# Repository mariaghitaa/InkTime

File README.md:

# Proiect InkTime Smartwatch

**Student:** Ghița Maria  
**Grupa:** 331CC

## 1. Descrierea Conceptului

InkTime este un dispozitiv purtabil bazat pe microcontrolerul **nRF52840**, conceput pentru a maximiza autonomia prin utilizarea unui ecran de tip **E-Paper (EPD)** de 1.54 inch. Spre deosebire de ecranele clasice, tehnologia E-Paper consumă energie doar la împrospătarea imaginii, oferind o vizibilitate excelentă în lumină naturală și un mod de operare "Always-on" extrem de eficient.

## 2. Diagrama Bloc (Hardware Architecture)

```text
                                  SISTEM INTELIGENT INKTIME
      SURSA ENERGIE              ___________________________                PERIFERICE (I/O)
    _________________           |                           |             ____________________
   |                 |          |      nRF52840 (SoC)       |            |                    |
   | USB-C Connector |--- 5V ---|   Bluetooth 5.0 Low En.   |--- SPI --->|  E-PAPER DISPLAY   |
   |   (Incarcare)   |          |___________________________|    Bus     |  (1.54" 24-pin)    |
   |_________________|           |  P0.02 (SCK)             |            |____________________|
            |                    |  P0.03 (MOSI)            |
            v                    |  P0.15 (DC)              |             ____________________
    _________________            |  P0.16 (RST)             |            |                    |
   | BQ25180 Charger |           |  P0.17 (BUSY)            |            |                    |
   | (Mngmnt Baterie)|-- VBAT -- |                          |            |                    |
   |_________________|    |      |  P0.26 (SDA) <---I2C---> |----------->|  ACCEL. (BMA421)   |
            ^             |      |  P0.27 (SCL)    Bus      |----------->|  GAUGE (MAX17048)  |
            |             |      |                          |----------->|  DRV2605 (Haptic)  |
    ________|________     |      |                          |            |____________________|
   | Li-Po Battery   |----+      |                          |
   |    250 mAh      |    |      |  P1.11 (PWM) ------------|----------->[ SHAKER / MOTOR ]
   |_________________|    |      |                          |
            |             |      |  P0.13 (UP)              |             ____________________
            v             |      |  P0.14 (ENTER) <---GPIO--|------------|   3x BUTOANE       |
    _________________     |      |  P1.02 (DOWN)            |            |   NAVIGATIE        |
   | RT6160A (Buck-B)|<---+      |                          |            |____________________|
   |  Output: 3.3V   |-----------|  P0.00 / P0.01 ----------|----------->[ CRYSTAL 32.768kHz]
   |_________________|           |  (LFXO Clock)            |            
                                 |__________________________|
```

## 3. Descriere Detaliată Hardware

### 3.1 Microcontroller — nRF52840

Inima sistemului este microcontrollerul Nordic nRF52840, care gestionează toate perifericele, comunicația wireless și logica aplicației.

- **CPU:** ARM Cortex-M4F la frecvență maximă de 64 MHz
- **Memorie:** 1 MB Flash, 256 KB RAM
- **Alimentare:** 3.3V (furnizat de regulatorul DC-DC)
- **Conectivitate:** Bluetooth 5.0 Low Energy, USB 2.0
- **Periferice utilizate:** SPI, I2C, GPIO, PWM, USB

Antena ceramică 2450AT18B100E (2.4 GHz) este acordată printr-o rețea de matching LC calculată pentru impedanță de 50Ω, asigurând performanță RF optimă.

### 3.2 Sistemul de Alimentare

#### Baterie LiPo

Dispozitivul este alimentat de o baterie LiPo cu tensiune nominală de 3.7V (max 4.2V) și capacitate de 250 mAh.

#### Încărcător — BQ25180

Încărcarea bateriei se realizează prin circuitul BQ25180 care primește alimentare de la conectorul USB-C. Acesta oferă management complet al ciclului de încărcare, protecție termică și reglare a curentului de încărcare pentru bateria LiPo. Comunicarea cu MCU-ul se face prin I2C, permițând configurarea parametrilor de încărcare din software.

#### Convertor DC-DC — RT6160A

Regulatorul buck-boost RT6160A convertește tensiunea variabilă a bateriei (3.0–4.2V) într-o ieșire stabilă de 3.3V. Alegerea unui convertor buck-boost (în loc de un LDO) asigură funcționarea stabilă a întregului sistem inclusiv când bateria este aproape descărcată. Tensiunea de 3.3V alimentează MCU-ul, senzorii, display-ul și toate celelalte periferice.

#### Fuel Gauge — MAX17048

Monitorizarea stării bateriei este realizată de MAX17048, care utilizează algoritmul ModelGauge pentru a estima nivelul de încărcare (State of Charge) fără a necesita rezistență de shunt. Comunicarea se face prin I2C, iar pinul ALERT (conectat la P0.10 pe MCU) poate genera o întrerupere atunci când nivelul bateriei scade sub un prag configurat.

### 3.3 Interfața USB-C

Conectorul USB Type-C (KH-TYPE-C-16P) îndeplinește două roluri: alimentare pentru încărcarea bateriei și comunicație USB 2.0 cu MCU-ul. Liniile de date D+ și D- sunt conectate la pinii USB dedicați ai nRF52840, iar pe liniile CC1/CC2 sunt montate rezistențe pull-down de 5.1kΩ pentru identificarea rolului de device. Protecția ESD pe liniile USB este asigurată de circuitul USBLC6-2SC6Y.

### 3.4 Display E-Paper

Display-ul e-paper de 1.54 inch este conectat prin FPC (conector Molex 503480-2400, 24-pin). Principalele avantaje ale tehnologiei e-paper pentru un smartwatch sunt consumul aproape zero în idle (imaginea persistă fără alimentare) și lizibilitatea excelentă în lumina solară.

Comunicarea cu MCU-ul se face prin **SPI** cu următoarele semnale:

- **MOSI** — transmite date și comenzi către display
- **SCK** — semnal de clock pentru sincronizarea transferului
- **DC** — diferențiază între comenzi și date
- **RST** — resetare hardware a controllerului display-ului
- **BUSY** — semnalizează că display-ul procesează un refresh

Alimentarea display-ului este controlată de un PFET Si2301CDS, permițând oprirea completă a panoului pentru economisirea energiei. Circuitul driver integrat pe placa EPD generează tensiunile înalte necesare actualizării cernelii electronice.

### 3.5 Accelerometru — BMA421

Senzorul BMA421 oferă măsurători de accelerație pe 3 axe și este utilizat pentru:

- detecția mișcării și a gesturilor (ridicare încheietură)
- funcționalitate de pedometru
- activarea ecranului din sleep

Comunicarea se face prin **I2C** (SDA, SCL), iar senzorul dispune de două linii de întrerupere (INT1, INT2) care permit trezirea MCU-ului din modul de consum redus doar când apare un eveniment relevant.

### 3.6 Driver Haptic — DRV2605

Driverul DRV2605 controlează motorul de vibrație (LRA/ERM) și oferă o bibliotecă de peste 100 de efecte haptice predefinite. Configurarea efectelor se realizează prin **I2C**, iar activarea vibrației se poate face și direct printr-un semnal digital pe pinul EN, fără a necesita comunicare I2C continuă.

### 3.7 Butoane

Trei butoane tactile (EVP-AKB31A) sunt conectate la pini GPIO ai MCU-ului cu rezistențe pull-up de 10kΩ. La apăsare, butonul conectează pinul la masă, iar MCU-ul detectează tranziția HIGH→LOW. Fiecare buton are un condensator de debouncing de 1µF.

- **UP** — navigare sus în meniu
- **ENTER** — selecție / confirmare
- **DOWN** — navigare jos în meniu

### 3.8 Interfața SWD

Programarea și debugging-ul firmware-ului se realizează prin interfața SWD (Serial Wire Debug) accesibilă printr-un header Tag-Connect TC2030-IDC (6-pin). Semnalele utilizate: SWDIO, SWDCLK, RESET, VCC, GND.

## 4. Bill of Materials (BOM)

| Componentă | Package | JLC Parts | Datasheet |
|------------|---------|-----------|-----------|
| Antenna (2450AT18B100E) | SMD 3216 | [C5179427](https://jlcpcb.com/partdetail/C5179427) | [Datasheet](https://www.johansontechnology.com/datasheets/2450AT18B100/2450AT18B100.pdf) |
| Charger (BQ25120YBGR) | DSBGA-9 | [C1682423](https://jlcpcb.com/partdetail/C1682423) | [Datasheet](https://www.ti.com/lit/ds/symlink/bq25180.pdf) |
| Haptic Driver (DRV2605LDGSR) | VSSOP-10 | [C527464](https://jlcpcb.com/partdetail/C527464) | [Datasheet](https://www.ti.com/lit/ds/symlink/drv2605l.pdf) |
| Buttons (EVP-AKB31A) | SMD tactile | [C2845028](https://jlcpcb.com/partdetail/C2845028) | [Datasheet](https://industrial.panasonic.com/cdbs/www-data/pdf/ATV0000/ATV0000CE3.pdf) |
| USB Type-C Connector (KH-TYPE-C-16P) | 16-pin SMD | [C2765186](https://jlcpcb.com/partdetail/C2765186) | [Datasheet](https://datasheet.lcsc.com/lcsc/2012121836_Kinghelm-KH-TYPE-C-16P_C2765186.pdf) |
| Fuel Gauge (MAX17048G+T10) | DFN-8 (2x2) | [C2682616](https://jlcpcb.com/partdetail/C2682616) | [Datasheet](https://www.analog.com/media/en/technical-documentation/data-sheets/MAX17048-MAX17049.pdf) |
| MCU (nRF52840-QIAA-R) | aQFN73 (7x7) | [C190794](https://jlcpcb.com/partdetail/C190794) | [Datasheet](https://docs.nordicsemi.com/) |
| Accelerometer (BMA421) | LGA-12 (2x2) | [C5242966](https://jlcpcb.com/partdetail/C5242966) | [Datasheet](https://www.bosch-sensortec.com/media/boschsensortec/downloads/datasheets/bst-bma421-ds004.pdf) |
| FPC Connector (Molex 503480-2400) | 24-pin 0.5mm FPC | [C2857168](https://jlcpcb.com/partdetail/C2857168) | [Datasheet](https://www.molex.com/en-us/products/part-detail/5034802400) |
| Buck-Boost Regulator (RT6160AWSC) | WLCSP-15 | [C7065276](https://jlcpcb.com/partdetail/C7065276) | [Datasheet](https://www.richtek.com/assets/product_file/RT6160A/DS6160A-05.pdf) |
| Vibration Motor (LCM102733605F) | Wire leads | [C7528006](https://jlcpcb.com/partdetail/C7528006) | [Datasheet](https://datasheet.lcsc.com/lcsc/2310131633_LCM-LCM1027B3605F_C7528806.pdf) |
| PFET EPD power (Si2301CDS) | SOT-23 | [C10487](https://jlcpcb.com/partdetail/C10487) | [Datasheet](https://www.vishay.com/docs/68749/si2301cds.pdf) |
| USB ESD Protection (USBLC6-2SC6Y) | SOT-23-6 | [C7519](https://jlcpcb.com/partdetail/C7519) | [Datasheet](https://www.st.com/resource/en/datasheet/usblc6-2.pdf) |
| SWD Debug Header (TC2030-IDC) | Tag-Connect 6-pin | - | - |
| Crystal 32 MHz | 2016 | - | - |
| Crystal 32.768 kHz | 3215 | - | - |
| Resistors x 2 10k | 0201 | - | - |
| Resistors x 2 5.1k | 0201 | - | - |
| Capacitors x 4 12pF | 0201 | - | - |
| Capacitors x 5 100nF | 0201 | - | - |
| Capacitors x 5 4.7uF | 0402 | - | - |
| Capacitors x 2 22uF | 0402 | - | - |
| Capacitors x 12 1uF | 0402 | - | - |
| Inductor 0.47uH | 2012 | - | - |
| Inductor 10uH | 0402 | - | - |
| E-Paper Display 1.54 inch | 24-pin FPC | - | - |
| LiPo Battery 250 mAh | - | - | - |

## 5. Alocare Pini nRF52840

### 5.1 Interfața SPI — Display E-Paper

| Pin | Semnal | Rol |
|-----|--------|-----|
| P0.02 | SCK | Clock SPI pentru transfer date către display |
| P0.03 | MOSI | Linie de date master → display |
| P0.15 | DC | Selecție date/comandă |
| P0.16 | RST | Reset hardware controller display |
| P0.17 | BUSY | Stare display (ocupat/liber) |

SPI a fost ales deoarece actualizarea display-ului e-paper necesită transferuri rapide de blocuri mari de date (framebuffer complet). Pinii P0.02 și P0.03 suportă mapare SPI flexibilă pe nRF52840, iar P0.15–P0.17 sunt pini GPIO adiacenți, simplificând rutarea pe PCB.

### 5.2 Magistrala I2C — Senzori și Management Energetic

| Pin | Semnal | Dispozitive conectate |
|-----|--------|-----------------------|
| P0.26 | SDA | BMA421, DRV2605, MAX17048, RT6160A, BQ25180 |
| P0.27 | SCL | BMA421, DRV2605, MAX17048, RT6160A, BQ25180 |

P0.26 și P0.27 sunt pini cu suport hardware I2C nativ (TWIM peripheral) pe nRF52840. Toate cele cinci dispozitive I2C sunt conectate pe aceeași magistrală, fiecare cu adresă unică, reducând numărul de pini utilizați. Pe liniile SDA și SCL sunt montate rezistențe pull-up la 3.3V.

### 5.3 Semnale Suplimentare Senzori

| Pin | Semnal | Rol |
|-----|--------|-----|
| P0.10 | ALERT (MAX17048) | Întrerupere la nivel critic baterie, permite trezirea MCU din sleep |
| P0.22 | EN (DRV2605) | Activare directă efect haptic fără comunicație I2C |

Pinii de întrerupere ai BMA421 (INT1, INT2) sunt de asemenea conectați la MCU, permițând detecția evenimentelor de mișcare fără polling continuu.

### 5.4 Butoane — GPIO

| Pin | Funcție | Detalii |
|-----|---------|---------|
| P0.13 | Button UP | Pull-up 10kΩ, debounce 1µF |
| P0.14 | Button ENTER | Pull-up 10kΩ, debounce 1µF |
| P1.02 | Button DOWN | Pull-up 10kΩ, debounce 1µF |

Pinii sunt configurați ca intrări digitale. Alegerea lor a ținut cont de disponibilitatea pe portul GPIO și de rutarea optimă pe PCB. Apăsarea butonului trage pinul la GND, iar MCU-ul detectează frontul descrescător.

### 5.5 USB

| Pin | Semnal |
|-----|--------|
| D+ (dedicat) | Linie de date USB+ |
| D- (dedicat) | Linie de date USB- |
| VBUS (dedicat) | Detecție alimentare USB |

Pinii USB sunt dedicați pe nRF52840 (nu sunt GPIO remapabili) și sunt conectați la conectorul USB-C prin circuitul de protecție ESD USBLC6-2SC6Y.

### 5.6 Alte Semnale

| Pin | Semnal | Rol |
|-----|--------|-----|
| P0.00 | XL1 | Cristal 32.768 kHz — clock RTC pentru timekeeping în sleep |
| P0.01 | XL2 | Cristal 32.768 kHz — pereche oscilator LFXO |
| SWDIO | SWD Data | Programare și debug firmware |
| SWDCLK | SWD Clock | Clock interfață debug |

P0.00 și P0.01 sunt singurii pini pe nRF52840 dedicați oscilatorului low-frequency (LFXO). Cristalul de 32.768 kHz permite funcționarea RTC-ului cu consum extrem de redus (~2 µA) în modul System ON sleep.

### 5.7 Criterii de Alocare

Distribuția pinilor a fost realizată ținând cont de:

- utilizarea interfețelor hardware native ale MCU-ului (SPI, I2C, USB, LFXO)
- gruparea semnalelor conexe pe pini adiacenți pentru simplificarea traseelor PCB
- disponibilitatea funcțiilor de întrerupere hardware pe pinii aleși
- minimizarea consumului prin posibilitatea de wake-up din sleep pe oricare din pinii GPIO utilizați

## 6. Estimare Consum de Energie

### Consum per componentă

| Componentă | Mod Sleep / Idle | Mod Activ |
|------------|-----------------|-----------|
| nRF52840 | ~2–5 µA (System ON sleep) | ~5–10 mA (CPU activ, radio oprit) |
| nRF52840 (BLE TX) | — | ~4.8 mA (transmisie la 0 dBm) |
| Display E-Paper | ~0 µA (imagine statică) | ~10–20 mA (în timpul refresh-ului) |
| BMA421 | ~14 µA (low-power mode) | ~160 µA (normal mode) |
| MAX17048 | ~50 µA (măsurare continuă) | ~50 µA |
| DRV2605 + Motor | ~0 µA (standby) | ~100 mA (vibrație activă) |
| RT6160A | ~15 µA (quiescent) | depinde de sarcină |
| BQ25180 | ~1 µA (mod ship) | depinde de curentul de încărcare |

### Scenariu tipic de utilizare

În funcționare normală (ecran static, BLE inactiv, fără vibrație), consumul este dominat de MCU în sleep și senzori:

| Componentă | Consum estimat |
|------------|---------------|
| MCU (sleep cu RTC) | ~5 µA |
| BMA421 (low-power) | ~14 µA |
| MAX17048 | ~50 µA |
| RT6160A (quiescent) | ~15 µA |
| **Total idle** | **~84 µA** |

Cu o baterie de 250 mAh, autonomia teoretică maximă în idle este:

**250.000 µAh / 84 µA ≈ 2.976 ore ≈ 124 zile**

Într-un scenariu realist (cu refresh-uri periodice ale ecranului, citiri BLE ocazionale și notificări haptice), consumul mediu estimat este de aproximativ **0.5–1 mA**, rezultând o autonomie de **10–20 zile** — competitivă cu smartwatch-urile e-paper comerciale.

## 7. Jurnal de Design și Fabricație

- **Proiectare PCB:** S-a optat pentru o configurație de 4 straturi (Signal-GND-VCC-Signal) pentru a asigura ecranarea electromagnetică și integritatea semnalului RF.
- **Miniaturizare:** Toate componentele pasive de decuplare din jurul nRF52840 sunt de mărime 0201, reducând dimensiunea finală a plăcii.
- **Design Mecanic:** Carcasa a fost modelată în Fusion 360 pentru a integra PCB-ul și bateria de 250mAh într-un profil compact, utilizând toleranțe strânse pentru montarea prin presare.

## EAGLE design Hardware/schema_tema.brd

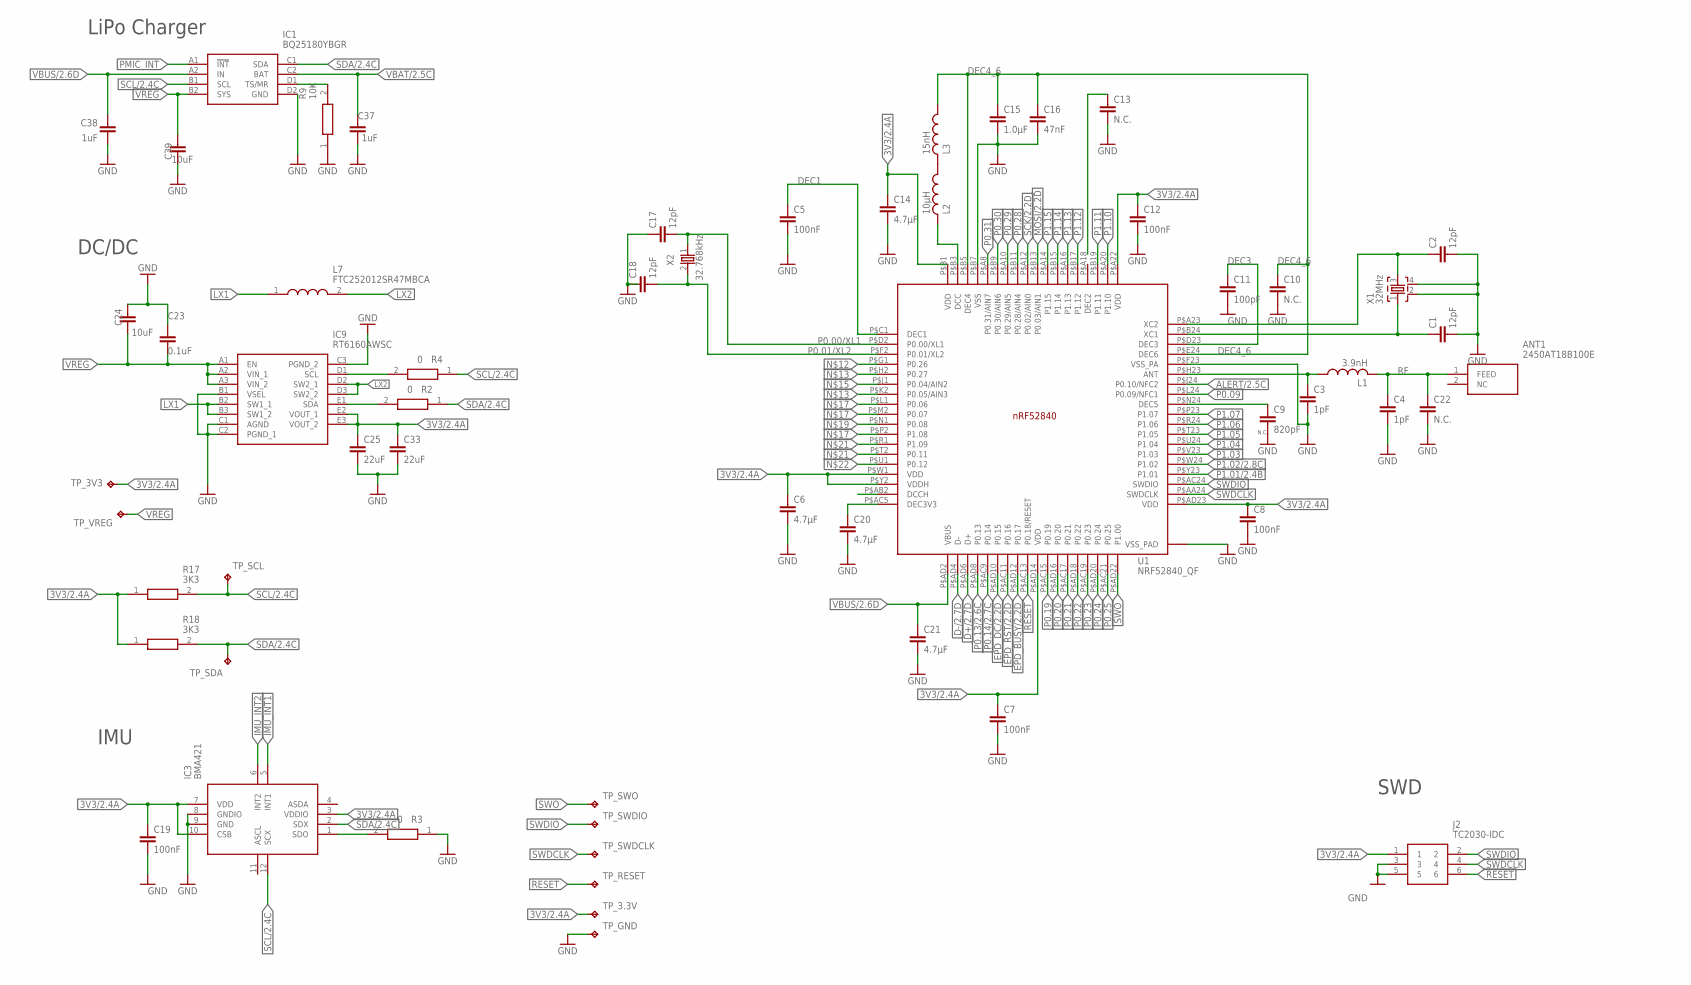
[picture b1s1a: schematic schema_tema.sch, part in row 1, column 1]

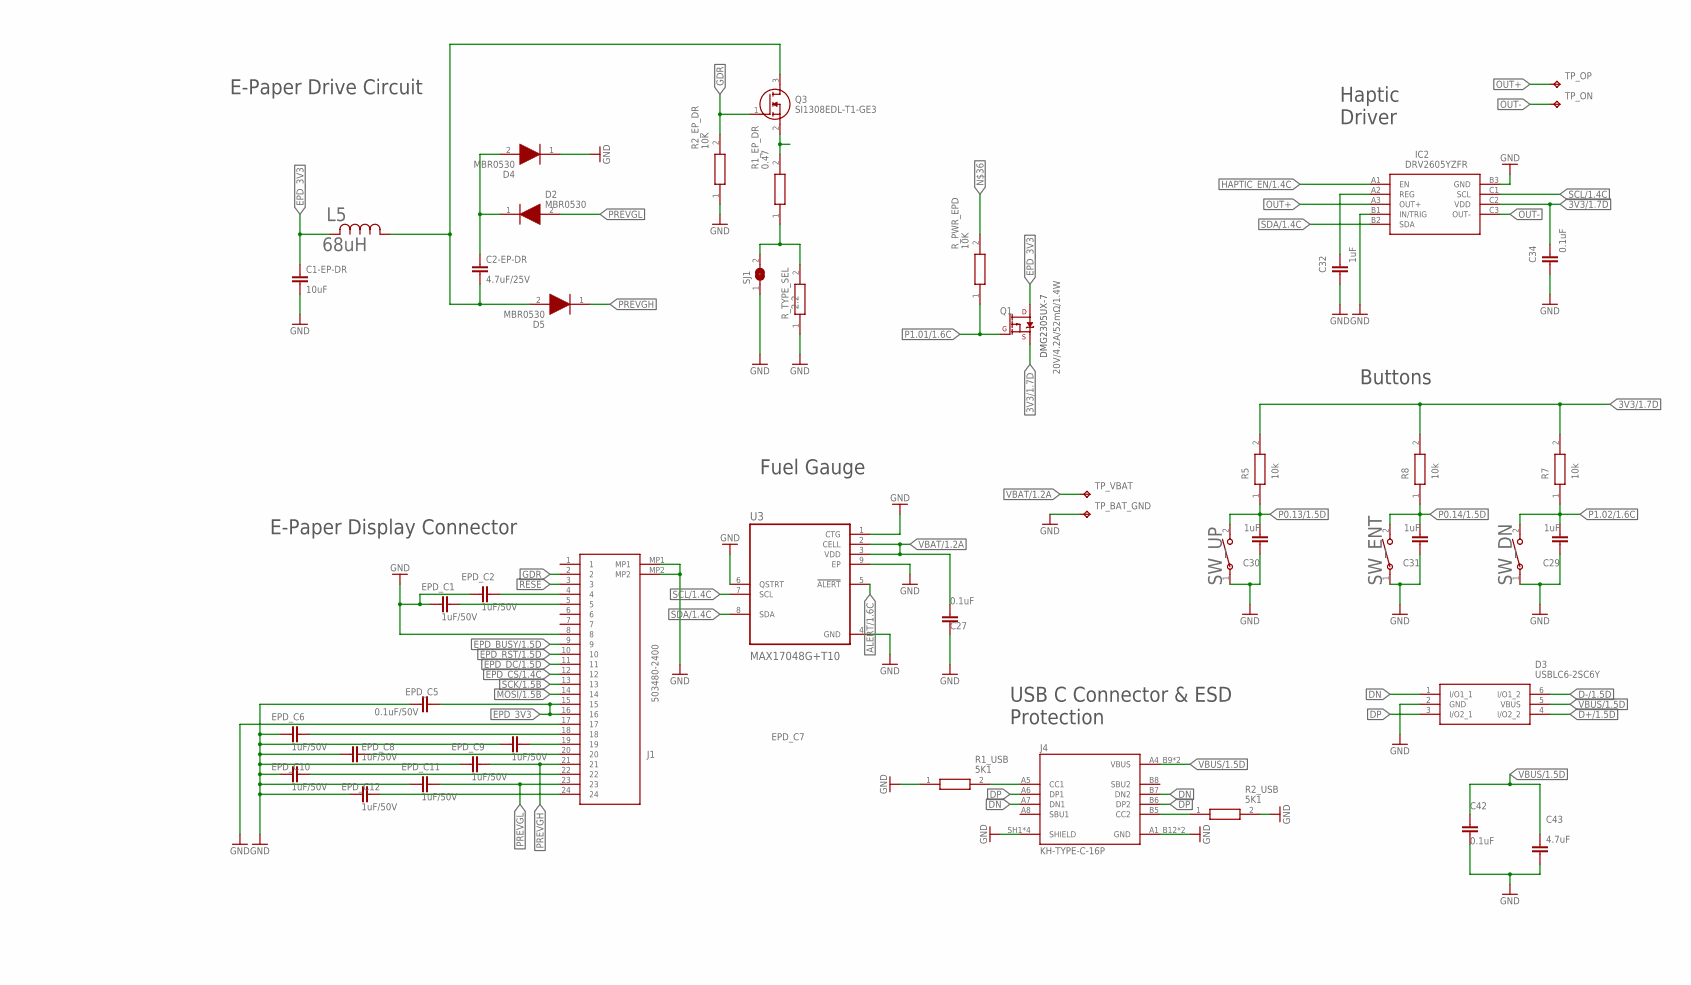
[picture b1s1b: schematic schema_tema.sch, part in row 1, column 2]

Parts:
ANT1: 2450AT18B100E; 2450AT18B100E_ANTC3216X140N
C1, C2, C17, C18: 12pF; NORDIC_NRF_3_RESC0201_L
C1-EP-DR, C39: 10uF; PERFECT_0402_0402
C2-EP-DR: 4.7uF/25V; PERFECT_0402_0402
C3, C4: 1pF; NORDIC_NRF_3_RESC0201_L
C5, C7, C8, C12, C19: 100nF; NORDIC_NRF_3_RESC0201_L
C6, C14, C20, C21: 4.7µF; PERFECT_0402_0402
C9: 820pF; NORDIC_NRF_3_RESC0201_L
C10, C13, C22: N.C.; NORDIC_NRF_3_RESC0201_L
C11: 100pF; NORDIC_NRF_3_RESC0201_L
C15: 1.0µF; PERFECT_0402_0402
C16: 47nF; NORDIC_NRF_3_RESC0201_L
C23, C27, C42: 0.1uF; NORDIC_NRF_3_RESC0201_L
C24: 10uF; NORDIC_NRF_3_RESC0201_L
C25, C33: 22uF; NORDIC_NRF_3_RESC0201_L
C29, C30, C31: 1uF; NORDIC_NRF_3_RESC0402_L
C32, C37, C38: 1uF; PERFECT_0402_0402
C34: 0.1uF; PERFECT_0402_0402
C43: 4.7uF; NORDIC_NRF_3_RESC0402_L
D2, D4, D5: MBR0530; ESP32_C6_LIBRARY_5_SOD3716X135N
D3: USBLC6-2SC6Y; ESP32_C6_LIBRARY_3_SOT95P280X145-6N
EPD_C1, EPD_C2, EPD_C6, EPD_C7, EPD_C8, EPD_C9, EPD_C10, EPD_C11, EPD_C12: 1uF/50V; PERFECT_0402_0402
EPD_C5: 0.1uF/50V; NORDIC_NRF_3_RESC0201_L
IC1: BQ25180YBGR; BQ25180YBGR_BGA8C40P2X4_100X155X50
IC2: DRV2605YZFR; DRV2605YZFR_BGA9C50P3X3_144X144X62
IC3: BMA421; BMA423_BMA423
IC9: RT6160AWSC; RT6160AWSC_BGA15C40P3X5_140X230X60
J1: 503480-2400; 503480-2400_5034802400
J2: TC2030-IDC; TC2030-IDC_TC2030IDC
J4: KH-TYPE-C-16P; KH-TYPE-C-16P_KINGHELM_KH-TYPE-C-16P
L1: 3.9nH; NORDIC_NRF_2_RESC0402_L
L2: 10µH; NORDIC_NRF_2_RESC0402_L
L3: 15nH; NORDIC_NRF_2_RESC0402_L
L5: 68uH; ESP32_C6_LIBRARY_2_IND_4828-WE-TPC_WRE
L7: FTC252012SR47MBCA; MLP2016SR47MT0S1_INDC2016X100N
Q1: 20V/4.2A/52mΩ/1.4W; ESP32_C6_LIBRARY_4_ESP32_C6_LIBRARY_4_ESP32_C6_LIBRARY_4_ES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
Q3: SI1308EDL-T1-GE3; ESP32_C6_LIBRARY_6_SOT65P210X110-3N
R1_EP_DR: 0.47; CPF0201D7K68C1_0201
R1_USB, R2_USB: 5K1; CPF0201D7K68C1_0201
R2, R3, R4: 0; CPF0201D7K68C1_0201
R2_EP_DR, R9: 10K; CPF0201D7K68C1_0201
R5, R7, R8: 10k; CPF0201D7K68C1_0201
R17, R18: 3K3; CPF0201D7K68C1_0201
R_PWR_EPD: 10K; CPF0201D7K68C1_0201
R_TYPE_SEL: 2.2; CPF0201D7K68C1_0201
SJ1: ESP32_C6_LIBRARY_7_JUMPER_SJ
SW_DN: 2025-10-22_07-23-44_LIBRARY_EVP-AKE31ASW_EVP-AKE3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; 2025-10-22_07-23-44_LIBRARY_SW_EVP-AKE31A_PAN
SW_ENT: 2025-10-22_07-23-44_LIBRARY_EVP-AKE31ASW_EVP-AKE3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; 2025-10-22_07-23-44_LIBRARY_SW_EVP-AKE31A_PAN
SW_UP: 2025-10-22_07-23-44_LIBRARY_EVP-AKE31ASW_EVP-AKE3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; 2025-10-22_07-23-44_LIBRARY_SW_EVP-AKE31A_PAN
TP_3.3V, TP_3V3: HECTOR_WATCH_1_TPTP20R; HECTOR_WATCH_1_TP20R
TP_BAT_GND: HECTOR_WATCH_1_TPTP20R; HECTOR_WATCH_1_TP20R
TP_GND: HECTOR_WATCH_1_TPTP20R; HECTOR_WATCH_1_TP20R
TP_ON: HECTOR_WATCH_1_TPTP20R; HECTOR_WATCH_1_TP20R
TP_OP: HECTOR_WATCH_1_TPTP20R; HECTOR_WATCH_1_TP20R
TP_RESET: HECTOR_WATCH_1_TPTP20R; HECTOR_WATCH_1_TP20R
TP_SCL: HECTOR_WATCH_1_TPTP20R; HECTOR_WATCH_1_TP20R
TP_SDA: HECTOR_WATCH_1_TPTP20R; HECTOR_WATCH_1_TP20R
TP_SWDCLK: HECTOR_WATCH_1_TPTP20R; HECTOR_WATCH_1_TP20R
TP_SWDIO: HECTOR_WATCH_1_TPTP20R; HECTOR_WATCH_1_TP20R
TP_SWO: HECTOR_WATCH_1_TPTP20R; HECTOR_WATCH_1_TP20R
TP_VBAT: HECTOR_WATCH_1_TPTP20R; HECTOR_WATCH_1_TP20R
TP_VREG: HECTOR_WATCH_1_TPTP20R; HECTOR_WATCH_1_TP20R
U1: NRF52840_QF; NORDIC_NRF_4_AQFN50P700X700X85_HS-74N
U3: MAX17048G+T10; ESP32_C6_LIBRARY_SON50P200X200X80-9N
X1: 32MHz; NORDIC_NRF_BT-XTAL_2016_N
X2: 32.768kHz; NORDIC_NRF_1_XTAL_3215_N

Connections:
3V3/1.7D: C34.1, IC2.C2 (VDD), Q1.2 (S), R5.2, R7.2, R8.2
3V3/2.4A: C6.1, C7.1, C8.1, C12.1, C14.1, C19.1, IC3.3 (VDDIO), IC3.7 (VDD), IC3.10 (CSB), J2.1, R17.1, R18.1, TP_3.3V.TP, TP_3V3.TP, U1.P$A22 (VDD), U1.P$AD14 (VDD), U1.P$AD23 (VDD), U1.P$B1 (VDD), U1.P$W1 (VDD), U1.P$Y2 (VDDH)
ALERT/1.6C: U3.5 (!ALERT)
ALERT/2.5C: U1.P$J24 (P0.10/NFC2)
D+/1.5D: D3.4 (I/O2_2)
D+/2.7D: U1.P$AD6 (D+)
D-/1.5D: D3.6 (I/O1_2)
D-/2.7D: U1.P$AD4 (D-)
DEC4_6: C10.1, C15.1, C16.1, L3.1, U1.P$B5 (DEC4), U1.P$E24 (DEC6)
DN: D3.1 (I/O1_1), J4.A7 (DN1), J4.B7 (DN2)
DP: D3.3 (I/O2_1), J4.A6 (DP1), J4.B6 (DP2)
EPD_3V3: C1-EP-DR.1, EPD_C5.2, J1.15, J1.16, L5.2, Q1.3 (D)
EPD_BUSY/1.5D: J1.9
EPD_BUSY/2.2D: U1.P$AD12 (P0.17)
EPD_CS/1.4C: J1.12
EPD_DC/1.5D: J1.11
EPD_DC/2.2D: U1.P$AD10 (P0.15)
EPD_RST/1.5D: J1.10
EPD_RST/2.2D: U1.P$AC11 (P0.16)
GDR: J1.2, Q3.1 (G), R2_EP_DR.2
GND: C1.2, C1-EP-DR.2, C2.2, C3.2, C4.2, C5.2, C6.2, C7.2, C8.2, C9.2, C10.2, C11.2, C12.2, C13.2, C14.2, C15.2, C16.2, C17.1, C18.1, C19.2, C20.2, C21.2, C22.2, C23.1, C24.2, C25.2, C27.2, C29.1, C30.1, C31.1, C32.2, C33.2, C34.2, C37.1, C38.1, C39.2, C42.2, C43.2, D3.2 (GND), D4.1 (K), EPD_C1.2, EPD_C2.2, EPD_C5.1, EPD_C6.2, EPD_C7.2, EPD_C8.2, EPD_C9.2, EPD_C10.2, EPD_C11.2, EPD_C12.2, IC1.D2 (GND), IC2.B1 (IN/TRIG), IC2.B3 (GND), IC3.8 (GNDIO), IC3.9 (GND), IC9.B1 (VSEL), IC9.C1 (AGND), IC9.C2 (PGND_1), IC9.C3 (PGND_2), J1.8, J1.17, J1.MP1, J1.MP2, J2.3, J2.5, J4.A1_B12 (GND), J4.A12_B1 (GND), J4.SH1 (SHIELD), J4.SH2 (SHIELD), J4.SH3 (SHIELD), J4.SH4 (SHIELD), R1_USB.1, R2_EP_DR.1, R2_USB.2, R3.1, R9.1, R_TYPE_SEL.1, SJ1.1, SW_DN.1, SW_ENT.1, SW_UP.1, TP_BAT_GND.TP, TP_GND.TP, U1.P$74 (VSS_PAD), U1.P$75 (VSS_PAD), U1.P$76 (VSS_PAD), U1.P$77 (VSS_PAD), U1.P$78 (VSS_PAD), U1.P$79 (VSS_PAD), U1.P$80 (VSS_PAD), U1.P$81 (VSS_PAD), U1.P$82 (VSS_PAD), U1.P$83 (VSS_PAD), U1.P$84 (VSS_PAD), U1.P$85 (VSS_PAD), U1.P$86 (VSS_PAD), U1.P$87 (VSS_PAD), U1.P$88 (VSS_PAD), U1.P$89 (VSS_PAD), U1.P$90 (VSS_PAD), U1.P$B7 (VSS), U1.P$F23 (VSS_PA), U3.1 (CTG), U3.4 (GND), U3.6 (QSTRT), U3.9 (EP), X1.2, X1.4
HAPTIC_EN/1.4C: IC2.A1 (EN)
IMU_INT1: IC3.5 (INT1)
IMU_INT2: IC3.6 (INT2)
LX1: IC9.B2 (SW1_1), IC9.B3 (SW1_2), L7.1
LX2: IC9.D2 (SW2_1), IC9.D3 (SW2_2), L7.2
MOSI/1.5B: J1.14
MOSI/2.2D: U1.P$B13 (P0.03/AIN1)
unnamed: IC9.D1 (SCL), R4.2
unnamed: IC9.E1 (SDA), R2.2
unnamed: C25.1, C33.1, IC9.E2 (VOUT_1), IC9.E3 (VOUT_2)
unnamed: IC1.D1 (TS/MR), R9.2
unnamed: C5.1, U1.P$C1 (DEC1)
unnamed: L2.2, U1.P$B3 (DCC)
unnamed: IC3.1 (SDO), R3.2
unnamed: L2.1, L3.2
unnamed: C11.1, U1.P$D23 (DEC3)
unnamed: C20.1, U1.P$AC5 (DEC3V3)
unnamed: C9.1, U1.P$N24 (DEC5)
unnamed: C2.1, U1.P$A23 (XC2), X1.3
unnamed: C1.1, U1.P$B24 (XC1), X1.1
unnamed: C3.1, L1.1, U1.P$H23 (ANT)
unnamed: C2-EP-DR.1, D2.1 (K), D4.2 (A)
unnamed: C2-EP-DR.2, D5.2 (A), L5.1, Q3.3 (D)
unnamed: Q3.2 (S), R1_EP_DR.2
unnamed: R1_EP_DR.1, R_TYPE_SEL.2, SJ1.2
unnamed: EPD_C1.1, J1.5
unnamed: C32.1, IC2.A2 (REG)
unnamed: EPD_C6.1, J1.18
unnamed: EPD_C7.1, J1.19
unnamed: EPD_C2.1, J1.4
unnamed: EPD_C8.1, J1.20
unnamed: J4.A5 (CC1), R1_USB.2
unnamed: EPD_C10.1, J1.22
unnamed: EPD_C12.1, J1.24
unnamed: J4.B5 (CC2), R2_USB.1
OUT+: IC2.A3 (OUT+), TP_OP.TP
OUT-: IC2.C3 (OUT-), TP_ON.TP
P0.00/XL1: C17.2, U1.P$D2 (P0.00/XL1), X2.1
P0.01/XL2: C18.2, U1.P$F2 (P0.01/XL2), X2.2
P0.09: U1.P$L24 (P0.09/NFC1)
P0.13/1.5D: C30.2, R5.1, SW_UP.2
P0.13/2.6C: U1.P$AD8 (P0.13)
P0.14/1.5D: C31.2, R8.1, SW_ENT.2
P0.14/2.7C: U1.P$AC9 (P0.14)
P0.19: U1.P$AC15 (P0.19)
P0.20: U1.P$AD16 (P0.20)
P0.21: U1.P$AC17 (P0.21)
P0.22: U1.P$AD18 (P0.22)
P0.23: U1.P$AC19 (P0.23)
P0.24: U1.P$AD20 (P0.24)
P0.25: U1.P$AC21 (P0.25)
P0.28: U1.P$B11 (P0.28/AIN4)
P0.29: U1.P$A10 (P0.29/AIN5)
P0.30: U1.P$B9 (P0.30/AIN6)
P0.31: U1.P$A8 (P0.31/AIN7)
P1.01/1.6C: Q1.1 (G), R_PWR_EPD.1
P1.01/2.4B: U1.P$Y23 (P1.01)
P1.02/1.6C: C29.2, R7.1, SW_DN.2
P1.02/2.8C: U1.P$W24 (P1.02)
P1.03: U1.P$V23 (P1.03)
P1.04: U1.P$U24 (P1.04)
P1.05: U1.P$T23 (P1.05)
P1.06: U1.P$R24 (P1.06)
P1.07: U1.P$P23 (P1.07)
P1.10: U1.P$A20 (P1.10)
P1.11: U1.P$B19 (P1.11)
P1.12: U1.P$B17 (P1.12)
P1.13: U1.P$A16 (P1.13)
P1.14: U1.P$B15 (P1.14)
P1.15: U1.P$A14 (P1.15)
PMIC_INT: IC1.A1 (!INT)
PREVGH: D5.1 (K), EPD_C9.1, J1.21
PREVGL: D2.2 (A), EPD_C11.1, J1.23
RESE: J1.3
RESET: J2.6, TP_RESET.TP, U1.P$AC13 (P0.18/RESET)
RF: ANT1.1 (FEED), C4.1, C22.1, L1.2
SCK/1.5B: J1.13
SCK/2.2D: U1.P$A12 (P0.02/AIN0)
SCL/1.4C: IC2.C1 (SCL), U3.7 (SCL)
SCL/2.4C: IC1.B1 (SCL), IC3.12 (SCX), R17.2, TP_SCL.TP
SDA/1.4C: IC2.B2 (SDA), U3.8 (SDA)
SDA/2.4C: IC1.C1 (SDA), IC3.2 (SDX), R18.2, TP_SDA.TP
SWDCLK: J2.4, TP_SWDCLK.TP, U1.P$AA24 (SWDCLK)
SWDIO: J2.2, TP_SWDIO.TP, U1.P$AC24 (SWDIO)
SWO: TP_SWO.TP, U1.P$AD22 (P1.00)
VBAT/1.2A: C27.1, TP_VBAT.TP, U3.2 (CELL), U3.3 (VDD)
VBAT/2.5C: C37.2, IC1.C2 (BAT)
VBUS/1.5D: C42.1, C43.1, D3.5 (VBUS), J4.A4_B9 (VBUS), J4.A9_B4 (VBUS)
VBUS/2.6D: C21.1, C38.2, IC1.A2 (IN), U1.P$AD2 (VBUS)
VREG: C23.2, C24.1, C39.1, IC1.B2 (SYS), IC9.A1 (EN), IC9.A2 (VIN_1), IC9.A3 (VIN_2), TP_VREG.TP

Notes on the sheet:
LiPo Charger
DC/DC
IMU
SWD
E-Paper Drive Circuit
DMG2305UX-7
Haptic Driver
E-Paper Display Connector
Buttons
Fuel Gauge
USB C Connector & ESD Protection
N.C.

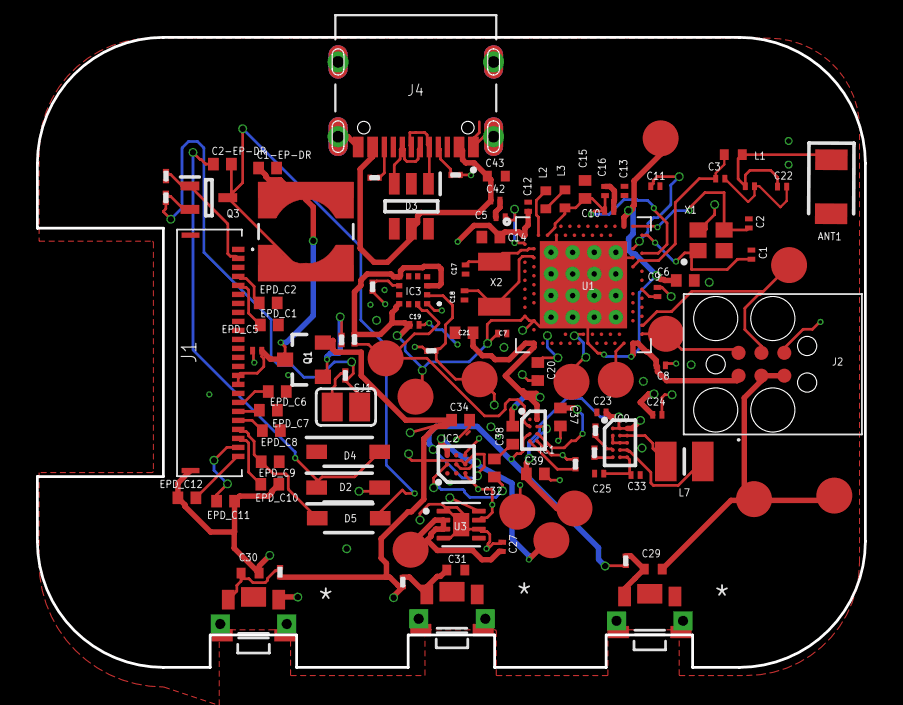
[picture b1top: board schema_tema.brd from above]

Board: 2 copper layers, 46.0 x 35.0 mm, 105 parts (0 on the bottom side), 62 nets.

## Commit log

2026-04-10 Adaugare fisiere
2026-04-10 Adaugare si step
2026-04-10 Adaugare readme si licenta
2026-04-10 modif readme
2026-04-21 final
2026-04-21 varianta finala

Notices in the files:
parts and their libraries:
COPYRIGHT: Copyright (C) 2024 Ultra Librarian. All rights reserved.
COPYRIGHT: Copyright (C) 2025 Ultra Librarian. All rights reserved.
